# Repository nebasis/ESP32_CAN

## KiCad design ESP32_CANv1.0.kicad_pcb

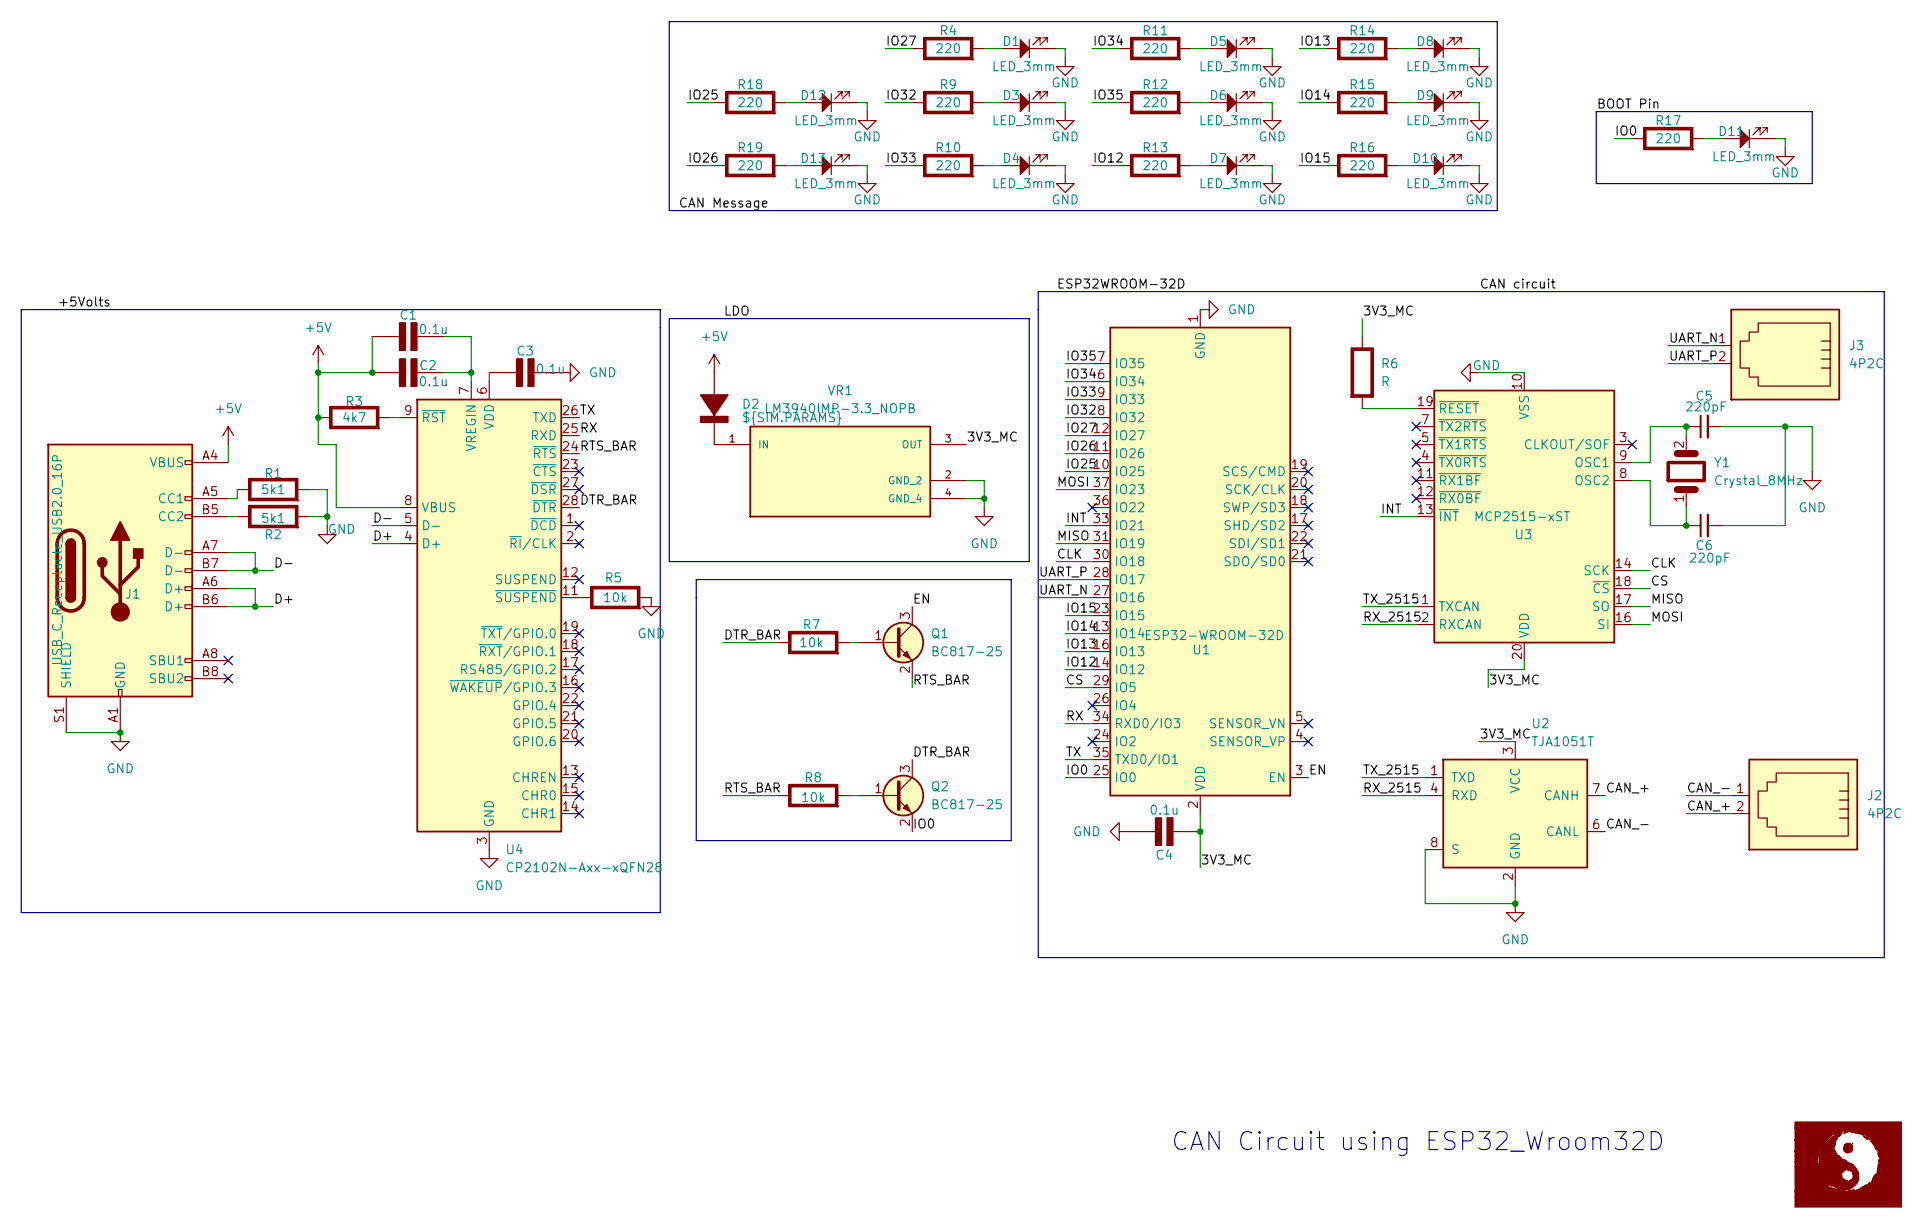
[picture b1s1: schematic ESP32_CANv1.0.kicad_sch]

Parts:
C1, C2, C3, C4: 0.1u; C_1206_3216Metric_Pad1.33x1.80mm_HandSolder; Rating V
C5, C6: 220pF_0603_25V; C_0603; Part Number CC0603JRNPO9BN221; JLCPCB ID C1603
D1, D3, D4, D5, D6, D7, D8, D9, D10, D11, D12, D13: LED_3mm; LED_1206_3216Metric_Pad1.42x1.75mm_HandSolder
D2: ${SIM.PARAMS}; LED_1206_3216Metric_Pad1.42x1.75mm_HandSolder; Rating V/A
J1: USB_C_Receptacle_USB2.0_16P; USB_C_Receptacle_GCT_USB4105-xx-A_16P_TopMnt_Horizontal
J2, J3: 4P2C; Hirose_DF3EA-02P-2H_1x02-1MP_P2.00mm_Horizontal
Q1, Q2: BC817-25; SOT-23
R1, R2: 5k1; R_1206_3216Metric_Pad1.30x1.75mm_HandSolder; Rating W
R3: 4k7; R_1206_3216Metric_Pad1.30x1.75mm_HandSolder; Rating W
R4, R9, R10, R11, R12, R13, R14, R15, R16, R17, R18, R19: 220; R_1206_3216Metric_Pad1.30x1.75mm_HandSolder; Rating W
R5, R7, R8: 10k; R_1206_3216Metric_Pad1.30x1.75mm_HandSolder; Rating W
R6: R; R_1206_3216Metric_Pad1.30x1.75mm_HandSolder; Rating W
U1: ESP32-WROOM-32D
U2: TJA1051T; SOIC-8_3.9x4.9mm_P1.27mm
U3: MCP2515-xST; TSSOP-20_4.4x6.5mm_P0.65mm
U4: CP2102N-Axx-xQFN28; QFN-28-1EP_5x5mm_P0.5mm_EP3.35x3.35mm
VR1: LM3940IMP-3.3_NOPB; VREG_LM3940IMP-3.3_NOPB; PARTREV G
Y1: Crystal_8MHz; Crystal_HC49-4H_Vertical

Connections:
+5V: C1.1 (+), C2.1 (+), D2.2 (A+), J1.A4 (VBUS), J1.A9 (VBUS), J1.B4 (VBUS), J1.B9 (VBUS), R3.1 (+), U4.8 (VBUS)
/3V3_MC: C4.2 (-), R6.1 (+), U1.2 (VDD), U2.3 (VCC), U3.20 (VDD), VR1.3 (OUT)
/CAN_+: J2.2, U2.7 (CANH)
/CAN_-: J2.1, U2.6 (CANL)
/CLK: U1.30 (IO18), U3.14 (SCK)
/CS: U1.29 (IO5), U3.18 (~CS)
/D+: J1.A6 (D+), J1.B6 (D+), U4.4 (D+)
/D-: J1.A7 (D-), J1.B7 (D-), U4.5 (D-)
/DTR_BAR: Q2.3 (C), R7.1 (+), U4.28 (~DTR)
/EN: Q1.3 (C), U1.3 (EN)
/INT: U1.33 (IO21), U3.13 (~INT)
/IO0: Q2.2 (E), R17.1 (+), U1.25 (IO0)
/IO12: R13.1 (+), U1.14 (IO12)
/IO13: R14.1 (+), U1.16 (IO13)
/IO14: R15.1 (+), U1.13 (IO14)
/IO15: R16.1 (+), U1.23 (IO15)
/IO25: R18.1 (+), U1.10 (IO25)
/IO26: R19.1 (+), U1.11 (IO26)
/IO27: R4.1 (+), U1.12 (IO27)
/IO32: R9.1 (+), U1.8 (IO32)
/IO33: R10.1 (+), U1.9 (IO33)
/IO34: R11.1 (+), U1.6 (IO34)
/IO35: R12.1 (+), U1.7 (IO35)
/MISO: U1.31 (IO19), U3.17 (SO)
/MOSI: U1.37 (IO23), U3.16 (SI)
/RTS_BAR: Q1.2 (E), R8.1 (+), U4.24 (~RTS)
/RX: U1.34 (RXD0/IO3), U4.25 (RXD)
/RX_2515: U2.4 (RXD), U3.2 (RXCAN)
/TX: U1.35 (TXD0/IO1), U4.26 (TXD)
/TX_2515: U2.1 (TXD), U3.1 (TXCAN)
/UART_N: J3.1, U1.27 (IO16)
/UART_P: J3.2, U1.28 (IO17)
GND: C3.2 (-), C4.1 (+), C5.2, C6.2, D1.1, D3.1, D4.1, D5.1, D6.1, D7.1, D8.1, D9.1, D10.1, D11.1, D12.1, D13.1, J1.A1 (GND), J1.A12 (GND), J1.B1 (GND), J1.B12 (GND), J1.S1 (SHIELD), R1.2 (-), R2.2 (-), R5.2 (-), U1.1 (GND), U1.15 (GND), U1.38 (GND), U1.39 (GND), U2.2 (GND), U2.8 (S), U3.10 (VSS), U4.3 (GND), U4.29 (GND), VR1.2 (GND_2), VR1.4 (GND_4)
unnamed: C1.2 (-), C2.2 (-), U4.7 (VREGIN)
unnamed: C3.1 (+), U4.6 (VDD)
unnamed: D2.1 (K-), VR1.1 (IN)
unnamed: J1.A5 (CC1), R1.1 (+)
unnamed: J1.B5 (CC2), R2.1 (+)
unnamed: Q1.1 (B), R7.2 (-)
unnamed: Q2.1 (B), R8.2 (-)
unnamed: R3.2 (-), U4.9 (~RST)
unnamed: D1.2, R4.2 (-)
unnamed: R5.1 (+), U4.11 (~SUSPEND)
unnamed: R6.2 (-), U3.19 (~RESET)
unnamed: D3.2, R9.2 (-)
unnamed: D4.2, R10.2 (-)
unnamed: D5.2, R11.2 (-)
unnamed: D6.2, R12.2 (-)
unnamed: D7.2, R13.2 (-)
unnamed: D8.2, R14.2 (-)
unnamed: D9.2, R15.2 (-)
unnamed: D10.2, R16.2 (-)
unnamed: D11.2, R17.2 (-)
unnamed: D12.2, R18.2 (-)
unnamed: D13.2, R19.2 (-)
unnamed: C5.1, U3.9 (OSC1), Y1.2
unnamed: C6.1, U3.8 (OSC2), Y1.1

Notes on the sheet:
CAN Circuit using ESP32_Wroom32D

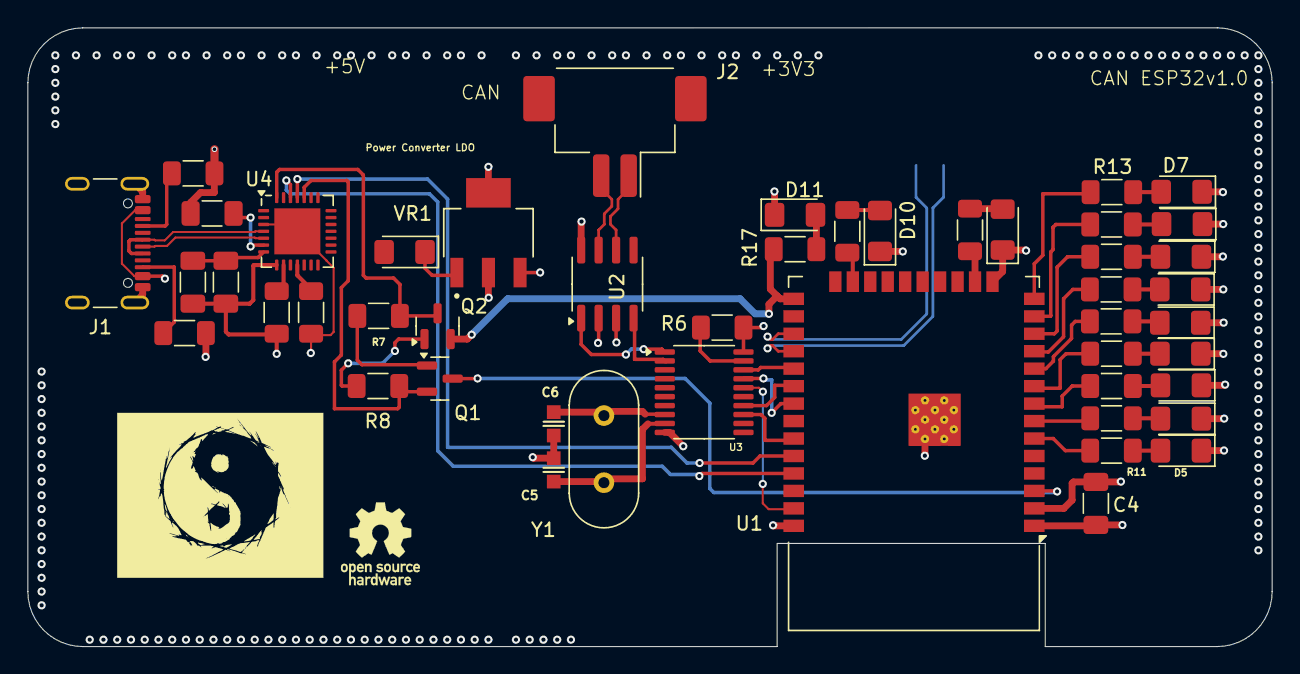
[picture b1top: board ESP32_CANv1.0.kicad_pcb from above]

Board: 4 copper layers, 90.5 x 45.0 mm, 49 parts (1 on the bottom side), 57 nets.
